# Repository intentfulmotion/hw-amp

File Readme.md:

# Amp Smart Lighting Controller

## Description

An ESP32 based lighting controller designed for lighting up bicycles, scooters, skateboards, and other micromobility.

## Features

* 3 axis, low noise, low zero-g error accelerometer (LIS2DHH12TR)
* Power supervisor + 2A regulated 3.3V output for long lengths of LEDs (WS2812B style or APA102 style leds)
* USB C Power Delivery compatible charging (does not implement the USB PD spec for higher charging rates)
* One button input connected to the ESP32 through the power supervisor
* One WS2812B LED for status onput
* LiPo charging @ 1A with charging and done charging indications
* Pin connections for LiPo battery with temperature sensing (2000 mAh recommended, 1000 mAh doable)
* MessagePack configuration for lighting strip setup
* Bluetooth LE for signaling indicators, brakes
* Customizable and scriptable lighting modes
* Over the Air updates over WiFi
* BLE Mesh (will be enabled in a future firmware update)
* Re-programmable over 6 pin programming header or via USB C so that you can load up your own firmware
* 4 channels of output (power + signal) for LED strips using JST-PH connectors (Qwiic connectors with different pin out)

## More Information

You can purchase a pre-assembled unit from the [Amp website](https://ridewithamp.com/store/amp-beta-0.5)

Alternatively, you can assemble a PCB with your preferred board manufacturer using the Gerbers provided in this repository or modify the project to your needs using the KiCad 5 project files.

## License

[Strong Reciprocal CERN Open Hardware License v2](License.md)

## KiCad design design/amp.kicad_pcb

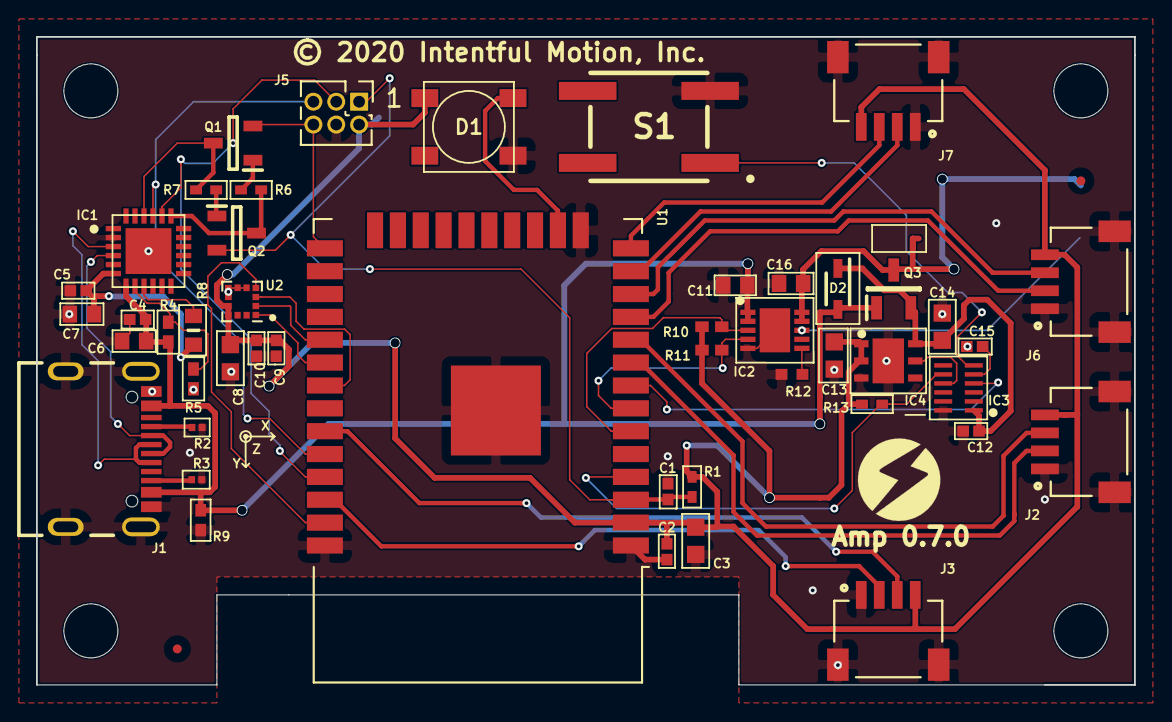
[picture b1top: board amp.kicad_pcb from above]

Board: 2 copper layers, 61.0 x 36.0 mm, 54 parts (1 on the bottom side), 42 nets.

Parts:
C1, C2, C4, C5, C9, C10, C12, C15: GRM155R61H104KE14D; CAPC1005X55N
C3, C8, C13, C14: GRM188R61A106KE69D; CAPC1608X95N
C6, C7, C11, C16: TMK107BJ105KA-T; CAPC1608X90N
D1: WS2812B; LED_WS2812B_PLCC4_5.0x5.0mm_P3.2mm
D2: BAT60AE6327HTSA1; SOD2513X110N
FID1, FID2: Fiducial; Fiducial_0.5mm_Mask1.5mm
H1, H2, H3, H4: MountingHole; MountingHole_3mm
IC1: CP2102N-A02-GQFN24R; QFN50P400X400X80-25N-D
IC2: MCP73833-FCI_MF; SON50P300X300X100-11N-D
IC3: STM6601CQ2BDM6F; SON50P200X300X80-12N-D
IC4: LD39200PU33R; SON95P300X300X100-7N-D
J1: USB4105-GF-A; GCT_USB4105-GF-A
J2, J3, J6, J7: SM04B-SRSS-TB(LF)(SN); JST_SM04B-SRSS-TB(LF)(SN)
J4: Conn_01x03_Female; SolderWirePad_1x03_P3.175mm_Drill0.8mm
J5: Conn_02x03_Odd_Even; PinHeader_2x03_P1.27mm_Vertical
Q1, Q2: PMBT2222,215; SOT95P230X110-3N
Q3: Si2347DS-T1-GE3; SOT95P237X112-3N
R1, R6, R7, R13: RC0402FR-0710KL
R2, R3: RC0201FR-075K1L; RESC0603X26N
R4: CRCW040222K6FKEDC; RESC1005X35N
R5: CRCW0402140RFKEDC; RESC1005X35N
R8: RC0603FR-101K2L; RESC1608X55N
R9: AC0402FR-13100KL-SamacSys_Parts; RESC1005X37N
R10, R11: RC0402FR-0710KL; RESC1005X40N
R12: RR0510P-102-D; RESC1005X40N
S1: EVQ-Q2U03W; EVQQ2
U1: ESP32-WROOM-32D; ESP32-WROOM-32
U2: LIS2HH12; LGA-12_2x2mm_P0.5mm

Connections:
+3V3: C2.2, C3.2, C8.1, C9.1, C10.1, C13.2, D1.1, IC4.1, IC4.2, J2.4, J3.4, J5.2, J6.4, J7.4, R1.2, R10.1, R11.1, R13.2, U1.2, U2.9, U2.10
/AMP_INPUT: IC3.8, R13.1, U1.4
/AMP_PWR_HLD: IC3.4, U1.8
/BAT_TEMP: IC2.8, J4.2
/CHARGE: IC2.3, R11.2, U1.6
/CLK: U1.30, U2.1
/CS: U1.29, U2.2
/D+: IC1.3, J1.A6, J1.B6
/D-: IC1.4, J1.A7, J1.B7
/DEBOUNCE: C15.1, IC3.5
/DONE: IC2.4, R10.2, U1.7
/DTR: IC1.22, Q1.3, R7.2
/GPIO0: J5.6, Q1.2, U1.25
/LED1_CLK: J3.2, U1.36
/LED1_DATA: J3.3, U1.33
/LED2_CLK: J2.2, U1.9
/LED2_DATA: J2.3, U1.10
/LED3_CLK: J6.2, U1.11
/LED3_DATA: J6.3, U1.12
/LED4_CLK: J7.2, U1.13
/LED4_DATA: J7.3, U1.14
/MISO: U1.31, U2.3
/MOSI: U1.37, U2.4
/PB_INPUT: IC3.6, S1.1
/POWER_ENABLE: IC3.9, IC4.5
/RESET: C1.1, J5.1, Q2.2, R1.1, U1.3
/RTS: IC1.19, Q2.3, R6.2
/RXD0: IC1.21, J5.5, U1.34
/STATUS_LED: D1.4, U1.16
/TXD0: IC1.20, J5.3, U1.35
/UART_VDD: C5.1, C7.1, IC1.6, R8.2
/VBAT: C16.1, IC2.9, IC2.10, J4.1, Q3.3
/VBUS: C4.1, C6.1, C11.2, D2.2, IC1.7, IC2.1, IC2.2, J1.A4/B9, J1.B4/A9, Q3.1, R4.1, R9.1
/V_FILTERED: C12.2, C14.2, D2.1, IC3.1, IC4.6, Q3.2
GND: C1.2, C2.1, C3.1, C4.2, C5.2, C6.2, C7.2, C8.2, C9.2, C10.2, C11.1, C12.1, C13.1, C14.1, C15.2, C16.2, D1.3, IC1.2, IC1.25, IC2.5, IC2.11, IC3.12, IC4.3, IC4.7, J1.A1/B12, J1.B1/A12, J1.G1, J1.G2, J1.G3, J1.G4, J2.1, J2.S1, J2.S2, J3.1, J3.S1, J3.S2, J4.3, J5.4, J6.1, J6.S1, J6.S2, J7.1, J7.S1, J7.S2, R2.1, R3.2, R5.2, R9.2, R12.2, S1.2, U1.1, U1.15, U1.38, U1.39, U2.5, U2.6, U2.7, U2.8
unnamed: IC1.8, R4.2, R5.1
unnamed: IC1.9, R8.1
unnamed: IC2.6, R12.1
unnamed: J1.A5, R2.2
unnamed: J1.B5, R3.1
unnamed: Q1.1, R6.1
unnamed: Q2.1, R7.1

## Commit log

2020-03-28 added led info
2020-03-28 added info about led channel output
2020-03-30 updated to new USB connector. Flipped status led and input button
2020-05-01 Fixes for CP2102N and LIS2DH12 circuitry. Swapped Futaba connectors for Qwiic style JST-PH connectors
2020-05-02 moved components to fit all connectors on the top layer
2020-05-02 removed bicolor led for charge and done. inputs redirected to ESP32
2020-05-02 added silkscreen logo to the front
2020-05-02 added bom
2020-05-02 fixed BOM listing for CP2102N RSTb resistors
2020-05-02 fixed schematic listing for R4 resistor
2020-05-02 fixed schematic version number
2020-05-02 Swapped out DIO5158 for MCP83733 (part shortage)
2020-05-02 extraneous net
2020-05-02 update board layout

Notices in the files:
design/amp.kicad_pcb:
© 2020 Intentful Motion, Inc.
parts and their libraries:
Copyright 2016 Accelerated Designs. All rights reserved.
